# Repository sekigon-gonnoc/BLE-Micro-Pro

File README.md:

# BLE-Micro-Pro

BLE Micro ProはPro Microとの互換性を意識した、nrf52840モジュール搭載のブレークアウトボードです。主に自作キーボードでの使用を想定して設計しています。Pro Microを使用した自作キーボードに取り付けてQMKベースの専用ファームウェアを書き込むことで、USB/BLE5の両方に対応させることができます。  

**質問等は [Self Made Keyboard in Japan の Discord](https://discordapp.com/invite/zXCss8T) #mon-shin🔰 (トラブルシューティング) または #ble-micro-pro（開発関係の質問）チャンネルまで。**
**質問の前に過去ログを参照してください**

## 販売リンク

[BOOTH](https://nogikes.booth.pm/items/1177319)  
[遊舎工房](https://yushakobo.jp/shop/ble-micro-pro/)

## 使用上の注意点

Pro Microとの互換性を意識して設計されていますが、以下の点にご注意ください。

- 入出力は3.3Vです。ただし、5・6番ピン(SDA・SCL)のみFETによるレベルシフト回路を実装しています。

- RAWピンの最大電圧は5Vです。

## 接続確認済みデバイス

Windows 10, Androidとの接続を確認しています。使用する機器との相性や使用環境によっては接続が不安定になることがあります。

## 使い方(ハードウェア編)

USBコネクタの横にあるBATピンから、あるいはUSBコネクタ、RAWピン、VCCピンから電源供給できます。

- BATピン (1.7V--3.6V)
- RAW, VCC (3V--5V)
  - ただし、RAW, VCC >= BAT

コンスルーに対応しているため、はんだ付けせずに基板に取り付けることも可能です。

21番ピンは5Vをダイオードで電圧降下させて4.3Vにしています。これは、WS2812などのシリアルLEDを3.3Vの信号で光らせるためです。
Helixなど24番ピンと21番ピンをショートさせているPCBの場合は、24番ピンのピンヘッダを抜き去ることでLEDが光るようになります。
LEDの電源を24番ピンからしか取っていないキーボードの場合は、はんだ付けをして21番ピンから電源を取るように改造してください。
前述のようにダイオードを挟んでいるので21・24番ピンがショートしていても壊れません。

ブートローダー書き込み済みの場合、BOOTピンをGNDに落としながら起動、あるいはファームウェアから呼び出すことでUSB経由でのファームウェアの書き込みができます。

ブートローダーを使わない場合は裏面に露出したパッドからSWDでファームウェアを書き込みます。

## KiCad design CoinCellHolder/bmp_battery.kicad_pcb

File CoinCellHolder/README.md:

# CR1632基板キット

CR1632を二個のせられます。並列的に繋いでいるので、1個の電池のみで動かすことも出来ます。

## 組み立て上の注意点

- コイン電池ホルダの突起を基板側のシルクに合わせる

- 電池ホルダ間のクリアランスが狭いのでショートしないようにする
- 電池ホルダの足を折り曲げると背が低くなる
- ダイオードの向きに注意(ダイオードのカソード(ラインが入ってるほう)がシルクのマーク側)
- 電源出力のマイナス側は出っ張らないようにする(電池の取り付け・取り外しができなくなる)
- 他の基板と接触する部分(作例だと裏面)はテープなどで絶縁する

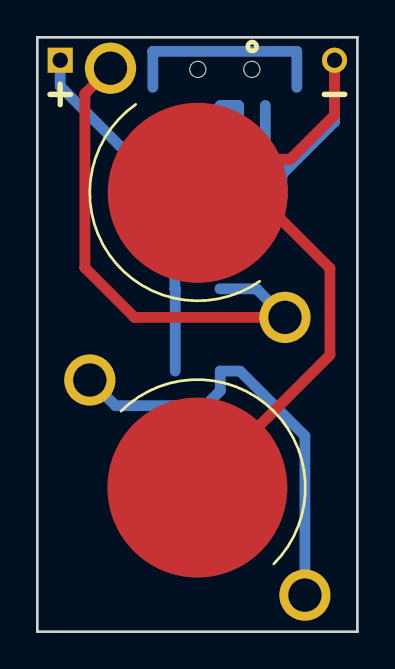
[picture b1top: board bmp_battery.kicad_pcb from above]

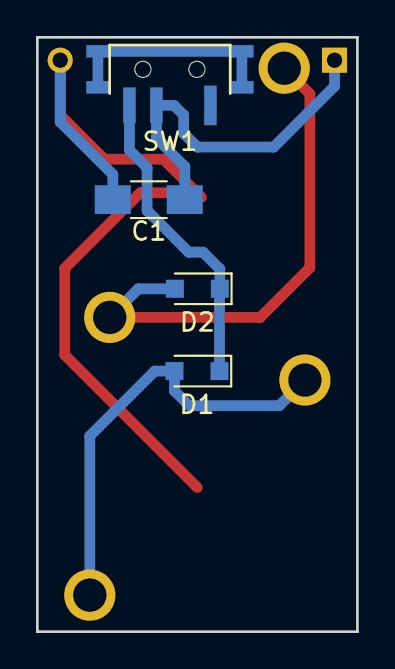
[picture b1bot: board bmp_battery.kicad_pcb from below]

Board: 2 copper layers, 17.8 x 33.0 mm, 8 parts (4 on the bottom side), 5 nets.

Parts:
BT1, BT2: Battery; ali_CR1632
C1: C_Small; C_1206_HandSoldering
D1, D2: D_Schottky_Small; D_SOD-323_HandSoldering
P1, P2: CONN_01X01; Pin_Header_Straight_1x01_Pitch2.54mm
SW1: SWITCH_INV; MK12C02

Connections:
GND: BT1.2, BT2.2, C1.2, P2.1
unnamed: BT1.1, D1.2
unnamed: BT2.1, D2.2
unnamed: C1.1, P1.1, SW1.2
unnamed: D1.1, D2.1, SW1.3

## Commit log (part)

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2018-10-05 Fix typo
2018-11-03 電池ホルダの説明を追加
2019-01-18 Add KiCad files of CoinCellHolder
2019-02-17 Add new bootloader file
    [Fix] Solve hash calculation problem causing error 0x0C on dfu
2019-09-15 Add folder: AboutDefaultFirmware
2019-09-15 Fix numatreus_rev1_config.h
2019-09-15 Fix ergo42_config_*.json
2019-09-16 fix numatreus confg
2019-09-16 #5 ビルドに関する記述を修正
2019-09-26 Move bootloader packages to Release page
2019-09-26 Document update for v0.2.0
2019-09-28 uf2ビルドオプションについて
2019-09-29 Add various config.json files
2019-09-29 Add config convert script from qmk source code to config.json
2019-09-29 set executable flag to config_converter.py
2019-10-06 Added Dozen0
2019-10-12 変換時にレイアウトを選べるようにした
2019-10-12 Ergodashのレイアウトを追加
2019-10-22 [fix]Layout選択時の行数がずれていたのを修正
2019-10-24 Update custom keycode
2019-10-26 Update doc
2019-10-28 スプリットキーボードのコンフィグ変換時にlpme用の設定を生成
2019-10-31 Fix error: 変換スクリプトのインデントがずれていたのを修正
2019-11-19 Add Keyboard Naked60/64
    各キーボードのdefaultとsalicylicのconfigとkeymapを追加
2019-11-19 Keymap Update
    一部のキーコードが間違っていた修正
2019-11-20 Keymap Update Naked60 / 64
    ・Naked60のピンをシングルに変更
    ・Naked60/64の全角半角キーをKC_ZHTGに変更
    ・ALT_TをLALT_Tに変更
2019-11-20 Add Keyboard Naked60/64 (#11)
    * Add Keyboard Naked60/64
    各キーボードのdefaultとsalicylicのconfigとkeymapを追加
    * Keymap Update
    一部のキーコードが間違っていた修正
    * Keymap Update Naked60 / 64
    ・Naked60のピンをシングルに変更
2019-11-20 Add keyboard 7sKB
    キーボード7sKBの以下のファイルを追加します。
    ・左右無線型、及びTRRS接続型のConfig
    ・USのdefaultマップ、及びJPのsalicylicマップ
2019-11-21 Add keyboard 7sKB (#12)
    キーボード7sKBの以下のファイルを追加します。
    ・左右無線型、及びTRRS接続型のConfig
    ・USのdefaultマップ、及びJPのsalicylicマップ
2019-11-23 Add helix_lpme
2019-11-29 Add LPME config files
2019-12-06 Add ble_micro_pro
2019-12-07 Update document
2019-12-23 add angel64
2019-12-23 add angel64 (#14)
2020-02-13 Fix invalid keycode
    KC_GRAVE -> KC_GRV
2020-02-14 Fix invalid keycode (#15)
    KC_GRAVE -> KC_GRV
2020-03-22 Update documents
2020-04-02 add bat43
2020-04-03 bugfix
2020-04-06 add bat43 (#16)
    * add bat43
    * bugfix
2020-04-08 Fix warnings
2020-04-10 変換スクリプトを修正
2020-04-11 rename config files
2020-04-14 Update 7skb_rev1_default.json (#17)
2020-04-17 Prepare document site
2020-04-26 create new keyboard rect44
2020-04-28 Modified default keymap
2020-05-02 Update docs
2020-05-06 add uzu42
2020-05-24 Fix ergo42 config
2020-06-05 Fix markdown notation
2020-06-05 Decorated the argument with "`"
    Because markdown is misinterpreted as an html tag
2020-06-06 Fix typo, markdown notation (#18)
    * Fix typo
    * Fix markdown notation
    * Decorated the argument with "`"
    Because markdown is misinterpreted as an html tag
2020-06-06 Add toybox config files
2020-06-20 Add keyboard JISplit89
    キーボード7sKBの以下のファイルを追加します。
    ・左右無線型のConfig
    ・JPのdefaultマップ
2020-06-21 Add keyboard JISplit89 (#21)
    キーボード7sKBの以下のファイルを追加します。
    ・左右無線型のConfig
    ・JPのdefaultマップ
2020-06-21 Update jisplit89_rev1_default.json
    キーマップの一部をコンフィギュレータに合わせて修正
2020-06-22 Update jisplit89_rev1_default.json (#22)
    キーマップの一部をコンフィギュレータに合わせて修正
2020-06-28 cols 7->6
2020-06-28 Claw44 fix cols (#23)
2020-07-12 ハードウェアの準備に情報を追加した
    なんか気になったので書いた
2020-07-17 コンスルーのピン数に関する記述を修正
2020-07-28 add rabbit capture plan
2020-08-21 Fix link
2020-09-05 Update design_guide.md
    NeoPixel系LEDの駆動に使えるピンについて記載
2020-09-24 Add Leftover30 keyboard
2020-09-25 change extension name
2020-09-25 update rev1
2020-09-25 rename rev1, add rev2
2020-09-25 rename
2020-09-25 add marksard keymap
2020-09-25 Update treadstone48 keyboard (#26)
    * update rev1
    * rename rev1, add rev2
    * rename
    * add marksard keymap
2020-09-25 Add leftover30 keyboard (#25)
    * Add Leftover30 keyboard
    * change extension name
    * rename
2020-10-05 Add rect44 kb (#27)
    * create new keyboard rect44
    * Modified default keymap
2020-11-07 AJisai74と7sPlusの追加及び微更新
    ■キーボード追加
    ・AJisai74
    ・7sPlus
    ■キーマップ更新
    ・JISplit89
    ・7sKB
2020-11-12 AJisai74と7sPlusの追加及び微更新(2回目)
    ■キーボード追加
    ・AJisai74
    ・7sPlus
    ■キーマップ更新
    ・JISplit89
    ・7sKB
2020-11-13 AJisai74と7sPlusの追加及び微更新(2回目) (#29)
    ■キーボード追加
    ・AJisai74
    ・7sPlus
    ■キーマップ更新
    ・JISplit89
    ・7sKB
2020-11-13 Fix invalid json file
2020-11-22 Add PistachioMacroPad
2020-11-29 uf2フォーマットのファームウェアによる書き込み方法を詳細化
2021-02-09 ErgoArrowsの追加
    以下のファイルを追加します。
    ergoarrows_lpme_left_config.json
    ergoarrows_master_left_config.json
    ergoarrows_slave_right_config.json
    ergoarrows_default.json
2021-02-22 add maJIStic keyboard
2021-02-22 add majistic's default keymap
2021-03-03 fix: Markdown format
2021-03-09 Add a new keyboard definition files of Lunakey Mini.
2021-03-10 Update the preparation section about setting Chrome.
2021-03-10 Add a Lunakey Mini row to the keyboard list.
2021-03-27 7sKB,JISplit89のVID/PID更新
    Remap対応のため7sKBとJISplit89をQMK側に合わせます。
2021-03-28 Update keyboard IDs
2021-05-28 add wings42
2021-05-28 Update VID/PID for bat43
2021-06-08 Create LICENSE
2021-06-27 add angel70
2021-07-01 Add owl8 keyboard
2021-07-04 Fixed a single quote in JSON that caused an error in the configurator.
2021-08-04 Reconstructed to not be skipped reading
2021-08-04 誤字修正
2021-08-04 空白があるとリンクにならなかったので見出しを変更
2021-08-04 Update files
2021-09-14 Change Lily58 VID PID
2021-10-05 Add Keyboard GL516
    GL516の三種を追加
    ・A52GL
    ・J73GL
    ・N51GL
2021-10-05 Naked48/60のVID/PIDを変更
    Naked48とNaked60のVID/PIDを変更します。
2021-10-11 PistachioMacroPadのVID/PIDを更新
2021-11-28 KeyFuda01_Tenkeyを追加
    設定ファイル：keyfuda01_tenkey.json
    初期キーマップファイル：keyfuda01_tenkey_default.json
2021-12-05 Add sticky4 keyboard
2021-12-05 KeyFuda02_mediaを追加
2022-04-01 config.jsonの解説にstartupの項目を追加
2022-05-08 miniZone config
2022-05-08 miniZone keymap
2022-05-08 キーマップを変更
2022-05-25 add Radialex
2022-06-18 Add Config
2022-06-18 キーマップを修正
2022-06-18 名前を変更
2022-06-18 右下のキー
2022-06-18 キーマップを追加
2022-06-18 USの左下を修正
2022-06-19 add duplex zone
2022-07-24 KeyFuda03_Stickの追加
2022-07-24 KeyFuda04の追加
2022-08-05 C48GLとO50GLの追加
2022-09-04 式で定義されたcol_num, row_numも扱えるように修正
2022-09-07 Add primer16/primer79
2022-10-18 add cannonball and handyman
2022-12-08 guide68の追加
2023-02-20 ロータリーエンコーダをRemapで変更できるように修正
    ロータリーエンコーダをRemapから変更できるように修正しました
2023-02-20 （KeyFuda03）ロータリーエンコーダをRemapで変更できるように修正
    ロータリーエンコーダをRemapから変更できるように修正しました
2023-02-25 add minidivide. covert from qmk
2023-03-22 update config
2023-03-22 minidivide
2023-07-21 add Ergo68
2023-08-15 kw49keys_config.json
2023-10-12 add primer61
2023-11-02 bmp-vial関連のファイルを追加
2023-11-10 アップロード
2023-11-11 Update config files
2023-11-17 Add docsify version plugin
2023-12-24 add cannonball and handyman
    in bmp-vial-config
2024-02-04 add minidivide max
2024-03-01 keymap
2024-03-17 KeyFuda02 and 03 added to new firmware
    I have finished verifying my KeyFuda02 and KeyFuda03 to the new firmware and will update them.
    I have confirmed that the change operation is possible with Remap.
    KeyFuda02とKeyFuda03の新しいファームウェアへの検証が終わったので更新します。
    Remapで変更操作が可能であることを確認しています。
2024-03-21 update Primer29&Primer61
2024-03-22 add vial.json
2024-03-22 Rename eeprom files
2024-04-08 Add Keyball39
2024-05-05 Modify bmp-vial-config/rect44_vial.json
2024-05-06 Adding BMP custom keycodes and DEFAULT.BIN for rect44
2024-05-29 KeyFuda01と04を追加
    KeyFuda01 TenkeyPad
    KeyFuda04 GridPad
    以上2つのマクロパッドの追加です。
    検証済みです。
2024-07-21 Add primer79
2024-07-21 upadte
2024-10-12 Add timothy
2024-10-22 ファイル名規則が異なっていたため修正
    なぜかBLE Micro Pro Web ConfiguratorでKeyFuda01の設定を書き込めなかった（404が出る）ので調べたらファイル名規則が違ったので修正します。
    Salicylic-acid3
    ↓
    salicylic_acid3
2024-11-26 7sProMaxを追加
2025-01-16 add palmslave
2025-01-16 古い設定ファイル
2025-01-16 Palmslaveのbmp-vial-config
2025-01-16 Revert "古い設定ファイル"
    This reverts commit 117097a3558021344d81cf58e09850657ee1ec70.
2025-01-16 デフォルトのキーマップ
2025-01-18 デフォルトのキーマップを変更しました。
2025-04-25 Add README and image for BMP Boost project
2025-05-14 キーマップの無線経由書き換えの説明を追加
2025-06-11 7sPro ELの追加
    7sPro ELを追加します。
    マスター、スレーブ、LPME-IOのコンフィグファイルを追加します。
2025-06-14 Vialのコンフィグファイルの追加
    7sPro ELのVial用コンフィグファイルを追加します。
    前回のPRで漏れていましたので追加します。
2025-07-11 BMP Boostの説明を更新
2025-08-01 Update README.md to include QMK to ZMK converter tool information
